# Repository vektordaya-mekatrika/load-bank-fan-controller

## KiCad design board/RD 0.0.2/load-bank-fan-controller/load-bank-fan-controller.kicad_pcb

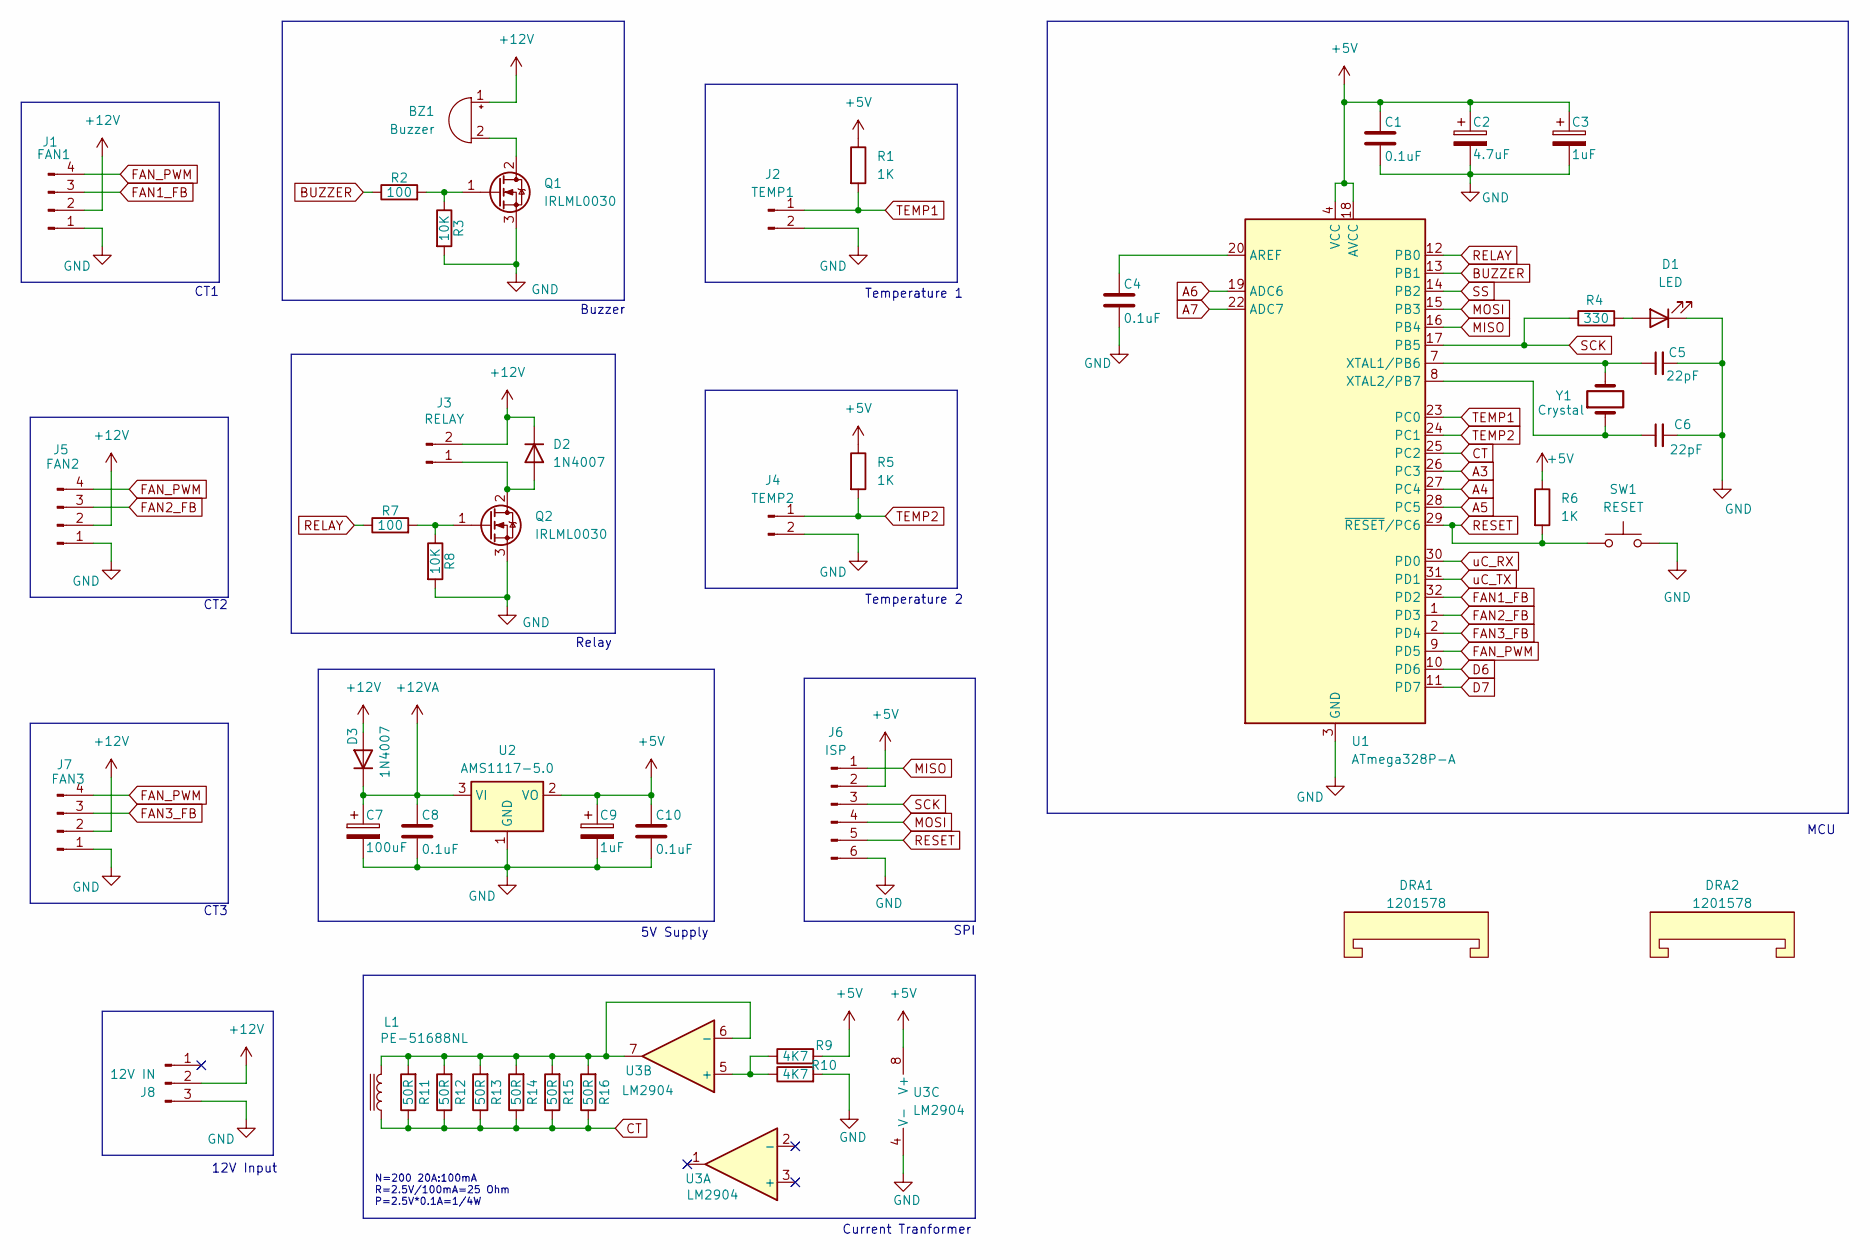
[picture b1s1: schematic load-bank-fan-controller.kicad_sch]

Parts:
BZ1: Buzzer; Buzzer_12x9.5RM7.6; Mfg PN TMB12A12; LCSC Part # DNP
C1, C4, C8, C10: 0.1uF; C_0603_1608Metric_Pad1.08x0.95mm_HandSolder; Mfg PN CC0603KRX7R8BB104; LCSC Part # C92490
C2: 4.7uF; C_0603_1608Metric_Pad1.08x0.95mm_HandSolder; Mfg PN CC0603KRX5R8BB475; LCSC Part # C326580
C3, C9: 1uF; C_0603_1608Metric_Pad1.08x0.95mm_HandSolder; Mfg PN CC0603KRX5R8BB105; LCSC Part # C14664
C5, C6: 22pF; C_0603_1608Metric_Pad1.08x0.95mm_HandSolder; Mfg PN CC0603JRNPO9BN220; LCSC Part # C105620
C7: 100uF; C_1210_3225Metric; Mfg PN EMK325ABJ107MM-T; LCSC Part # C394395
D1: LED; LED_0603_1608Metric_Pad1.05x0.95mm_HandSolder; Mfg PN LTST-C190GKT; LCSC Part # C125093
D2, D3: 1N4007; D_SOD-123F; Mfg PN 1N4007 A7; LCSC Part # C2902912
DRA1, DRA2: 1201578; DINRailAdapter_3xM3_PhoenixContact_1201578; Mfg PN 1201578; LCSC Part # C3019632
J1: FAN1; Molex_KK-254_AE-6410-04A_1x04_P2.54mm_Vertical; Mfg PN XD-2510-4A; LCSC Part # C17700994
J2: TEMP1; JST_XH_B2B-XH-A_1x02_P2.50mm_Vertical; Mfg PN ZX-XH2.54-2PZZ; LCSC Part # DNP
J3: RELAY; TerminalBlock_RND_205-00232_1x02_P5.08mm_Horizontal; Mfg PN WJ500V-5.08-2P; LCSC Part # C8465
J4: TEMP2; JST_XH_B2B-XH-A_1x02_P2.50mm_Vertical; Mfg PN ZX-XH2.54-2PZZ; LCSC Part # DNP
J5: FAN2; Molex_KK-254_AE-6410-04A_1x04_P2.54mm_Vertical; Mfg PN XD-2510-4A; LCSC Part # C17700994
J6: ISP; PinHeader_2x03_P2.54mm_Vertical; Mfg PN ZX-PZ2.54-2-3PZZ; LCSC Part # C7501274
J7: FAN3; Molex_KK-254_AE-6410-04A_1x04_P2.54mm_Vertical; Mfg PN XD-2510-4A; LCSC Part # DNP
J8: 12V IN; JST_VH_B3P-VH-B_1x03_P3.96mm_Vertical; Mfg PN HX VH3.96-3P ZZ; LCSC Part # C7435583
L1: PE-51688NL; PE51688NL; Mfg PN PE-51688NL; LCSC Part # C5718373
Q1, Q2: IRLML0030; SOT-23; Mfg PN IRLML0030TRPBF; LCSC Part # C67272
R1, R5, R6: 1K; R_0603_1608Metric_Pad0.98x0.95mm_HandSolder; Mfg PN RC0603FR-071KL; LCSC Part # C22548
R2, R7: 100; R_0603_1608Metric_Pad0.98x0.95mm_HandSolder; Mfg PN RC0603FR-07100RL; LCSC Part # C105588
R3, R8: 10K; R_0603_1608Metric_Pad0.98x0.95mm_HandSolder; Mfg PN RC0603FR-0710KL; LCSC Part # C98220
R4: 330; R_0603_1608Metric_Pad0.98x0.95mm_HandSolder; Mfg PN RC0603FR-07330RL; LCSC Part # C105881
R9, R10: 4K7; R_0603_1608Metric_Pad0.98x0.95mm_HandSolder; Mfg PN RC0603FR-074K7L; LCSC Part # C99782
R11, R12, R13, R14, R15, R16: 50R; R_MiniMELF_MMA-0204; Mfg PN CSR0204FTDV0500; LCSC Part # C489412
SW1: RESET; SW_Tactile_SPST_NO_Straight_CK_PTS636Sx25SMTRLFS; Mfg PN TS-1101-C-W; LCSC Part # C318938
U1: ATmega328P-A; TQFP-32_7x7mm_P0.8mm; Mfg PN ATmega328P-A; LCSC Part # C14877
U2: AMS1117-5.0; SOT-223-3_TabPin2; Mfg PN AMS1117-5.0; LCSC Part # C6187
U3: LM2904; SO-8_3.9x4.9mm_P1.27mm; Mfg PN LM2904DT; LCSC Part # C105411
Y1: Crystal; Crystal_HC49-U_Vertical; Mfg PN X49SD16MSD2SC; LCSC Part # C16212

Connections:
+5V: C1.1, C2.1, C3.1, C9.1, C10.1, J6.2, R1.1, R5.1, R6.1, R9.2, U1.4 (VCC), U1.6 (VCC), U1.18 (AVCC), U2.2 (VO), U3.8 (V+)
+12V: BZ1.1 (+), D2.1 (K), D3.2 (A), J1.2, J3.2, J5.2, J7.2, J8.2
+12VA: C7.1, C8.1, D3.1 (K), U2.3 (VI)
A3: U1.26 (PC3)
A4: U1.27 (PC4)
A5: U1.28 (PC5)
A6: U1.19 (ADC6)
A7: U1.22 (ADC7)
BUZZER: R2.1, U1.13 (PB1)
CT: L1.1, R11.1, R12.1, R13.1, R14.1, R15.1, R16.1, U1.25 (PC2)
D6: U1.10 (PD6)
D7: U1.11 (PD7)
FAN1_FB: J1.3, U1.32 (PD2)
FAN2_FB: J5.3, U1.1 (PD3)
FAN3_FB: J7.3, U1.2 (PD4)
FAN_PWM: J1.4, J5.4, J7.4, U1.9 (PD5)
GND: C1.2, C2.2, C3.2, C4.2, C5.2, C6.2, C7.2, C8.2, C9.2, C10.2, D1.1 (K), J1.1, J2.2, J4.2, J5.1, J6.6, J7.1, J8.3, Q1.3 (S), Q2.3 (S), R3.2, R8.2, R10.2, SW1.2, U1.3 (GND), U1.5 (GND), U1.21 (GND), U2.1 (GND), U3.4 (V-)
MISO: J6.1, U1.16 (PB4)
MOSI: J6.4, U1.15 (PB3)
unnamed: BZ1.2 (-), Q1.2 (D)
unnamed: D1.2 (A), R4.2
unnamed: D2.2 (A), J3.1, Q2.2 (D)
unnamed: Q1.1 (G), R2.2, R3.1
unnamed: Q2.1 (G), R7.2, R8.1
unnamed: C4.1, U1.20 (AREF)
unnamed: C5.1, U1.7 (XTAL1/PB6), Y1.2
unnamed: C6.1, U1.8 (XTAL2/PB7), Y1.1
unnamed: R9.1, R10.1, U3.5 (+)
unnamed: L1.2, R11.2, R12.2, R13.2, R14.2, R15.2, R16.2, U3.6 (-), U3.7
RELAY: R7.1, U1.12 (PB0)
RESET: J6.5, R6.2, SW1.1, U1.29 (~RESET/PC6)
SCK: J6.3, R4.1, U1.17 (PB5)
SS: U1.14 (PB2)
TEMP1: J2.1, R1.2, U1.23 (PC0)
TEMP2: J4.1, R5.2, U1.24 (PC1)
uC_RX: U1.30 (PD0)
uC_TX: U1.31 (PD1)

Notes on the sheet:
CT2
Current Tranformer
Temperature 1
12V Input
CT3
Buzzer
CT1
Relay
N=200 20A:100mA R=2.5V/100mA=25 Ohm P=2.5V*0.1A=1/4W
Temperature 2
5V Supply
SPI
MCU

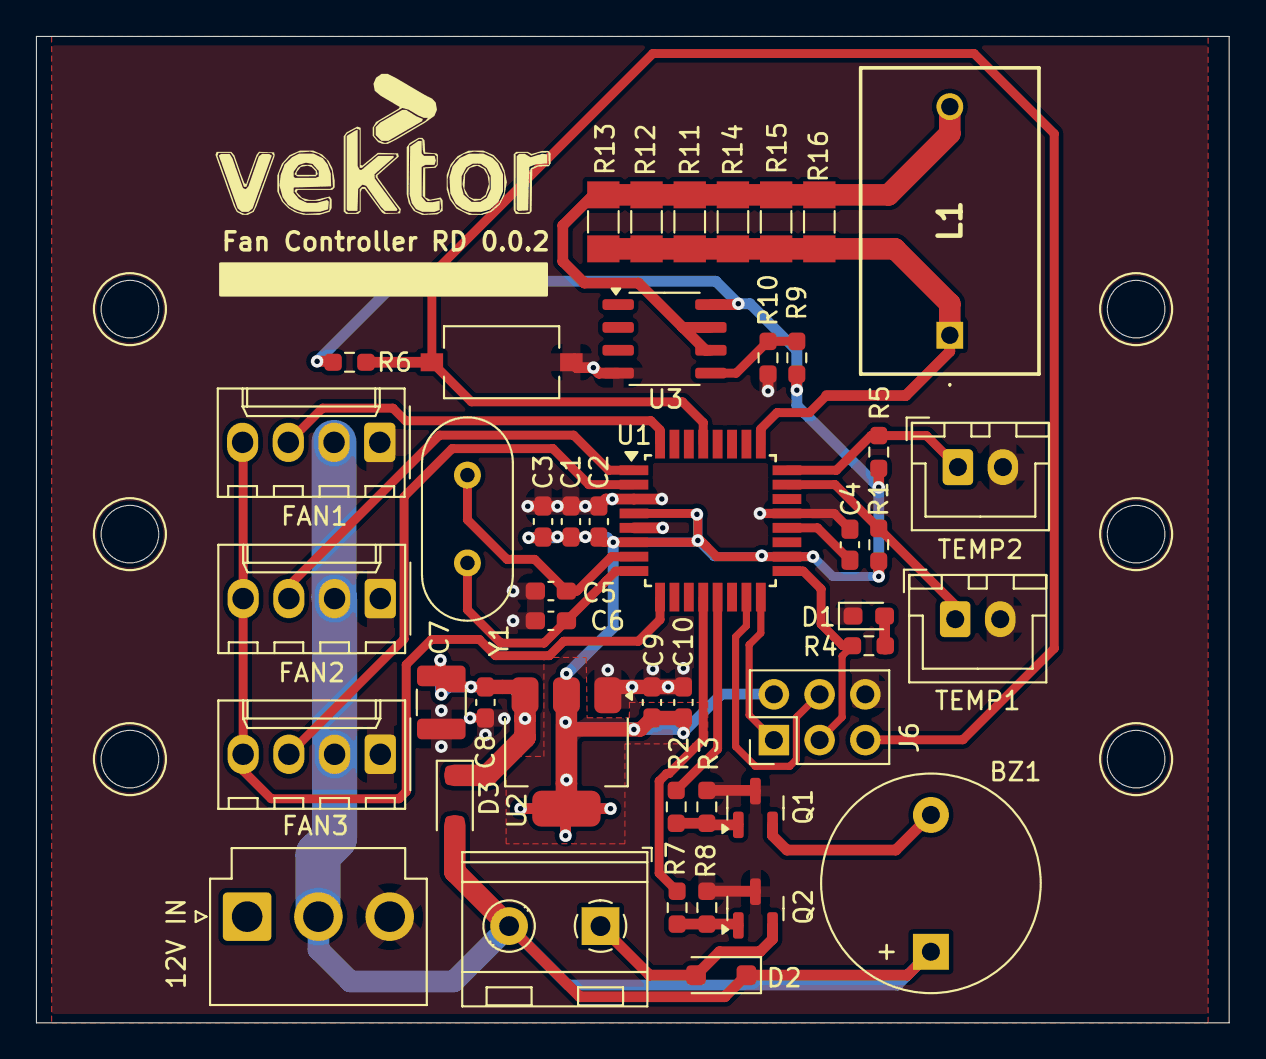
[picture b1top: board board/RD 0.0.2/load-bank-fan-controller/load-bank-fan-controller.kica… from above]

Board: 2 copper layers, 66.3 x 54.8 mm, 48 parts (0 on the bottom side), 27 nets.

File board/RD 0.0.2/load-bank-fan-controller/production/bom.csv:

Designator,Footprint,Quantity,Value,LCSC Part #
BZ1,Buzzer_12x9.5RM7.6,1,Buzzer,DNP
"C1, C10, C4, C8",0603,4,0.1uF,C92490
C2,0603,1,4.7uF,C326580
"C3, C9",0603,2,1uF,C14664
"C5, C6",0603,2,22pF,C105620
C7,1210,1,100uF,C394395
D1,0603,1,LED,C125093
"D2, D3",D_SOD-123F,2,1N4007,C2902912
"DRA1, DRA2",DINRailAdapter_3xM3_PhoenixContact_1201578,2,1201578,C3019632
J1,Molex_KK-254_AE-6410-04A_1x04_P2.54mm_Vertical,1,FAN1,C17700994 
J2,JST_XH_B2B-XH-A_1x02_P2.50mm_Vertical,1,TEMP1,DNP
J3,TerminalBlock_RND_205-00232_1x02_P5.08mm_Horizontal,1,RELAY, C8465
J4,JST_XH_B2B-XH-A_1x02_P2.50mm_Vertical,1,TEMP2,DNP
J5,Molex_KK-254_AE-6410-04A_1x04_P2.54mm_Vertical,1,FAN2,C17700994 
J6,PinHeader_2x03_P2.54mm_Vertical,1,ISP,C7501274
J7,Molex_KK-254_AE-6410-04A_1x04_P2.54mm_Vertical,1,FAN3,DNP
J8,JST_VH_B3P-VH-B_1x03_P3.96mm_Vertical,1,12V IN, C7435583
L1,PE51688NL,1,PE-51688NL,C5718373
"Q1, Q2",SOT-23,2,IRLML0030,C67272
"R1, R5, R6",0603,3,1K,C22548
"R10, R9",0603,2,4K7,C99782
"R11, R12, R13, R14, R15, R16",R_MiniMELF_MMA-0204,6,50R, C489412
"R2, R7",0603,2,100,C105588
"R3, R8",0603,2,10K,C98220
R4,0603,1,330,C105881
SW1,SW_Tactile_SPST_NO_Straight_CK_PTS636Sx25SMTRLFS,1,RESET,C318938
U1,TQFP-32_7x7mm_P0.8mm,1,ATmega328P-A,C14877
U2,SOT-223-3_TabPin2,1,AMS1117-5.0,C6187
U3,SO-8_3.9x4.9mm_P1.27mm,1,LM2904,C105411
Y1,Crystal_HC49-U_Vertical,1,Crystal, C16212

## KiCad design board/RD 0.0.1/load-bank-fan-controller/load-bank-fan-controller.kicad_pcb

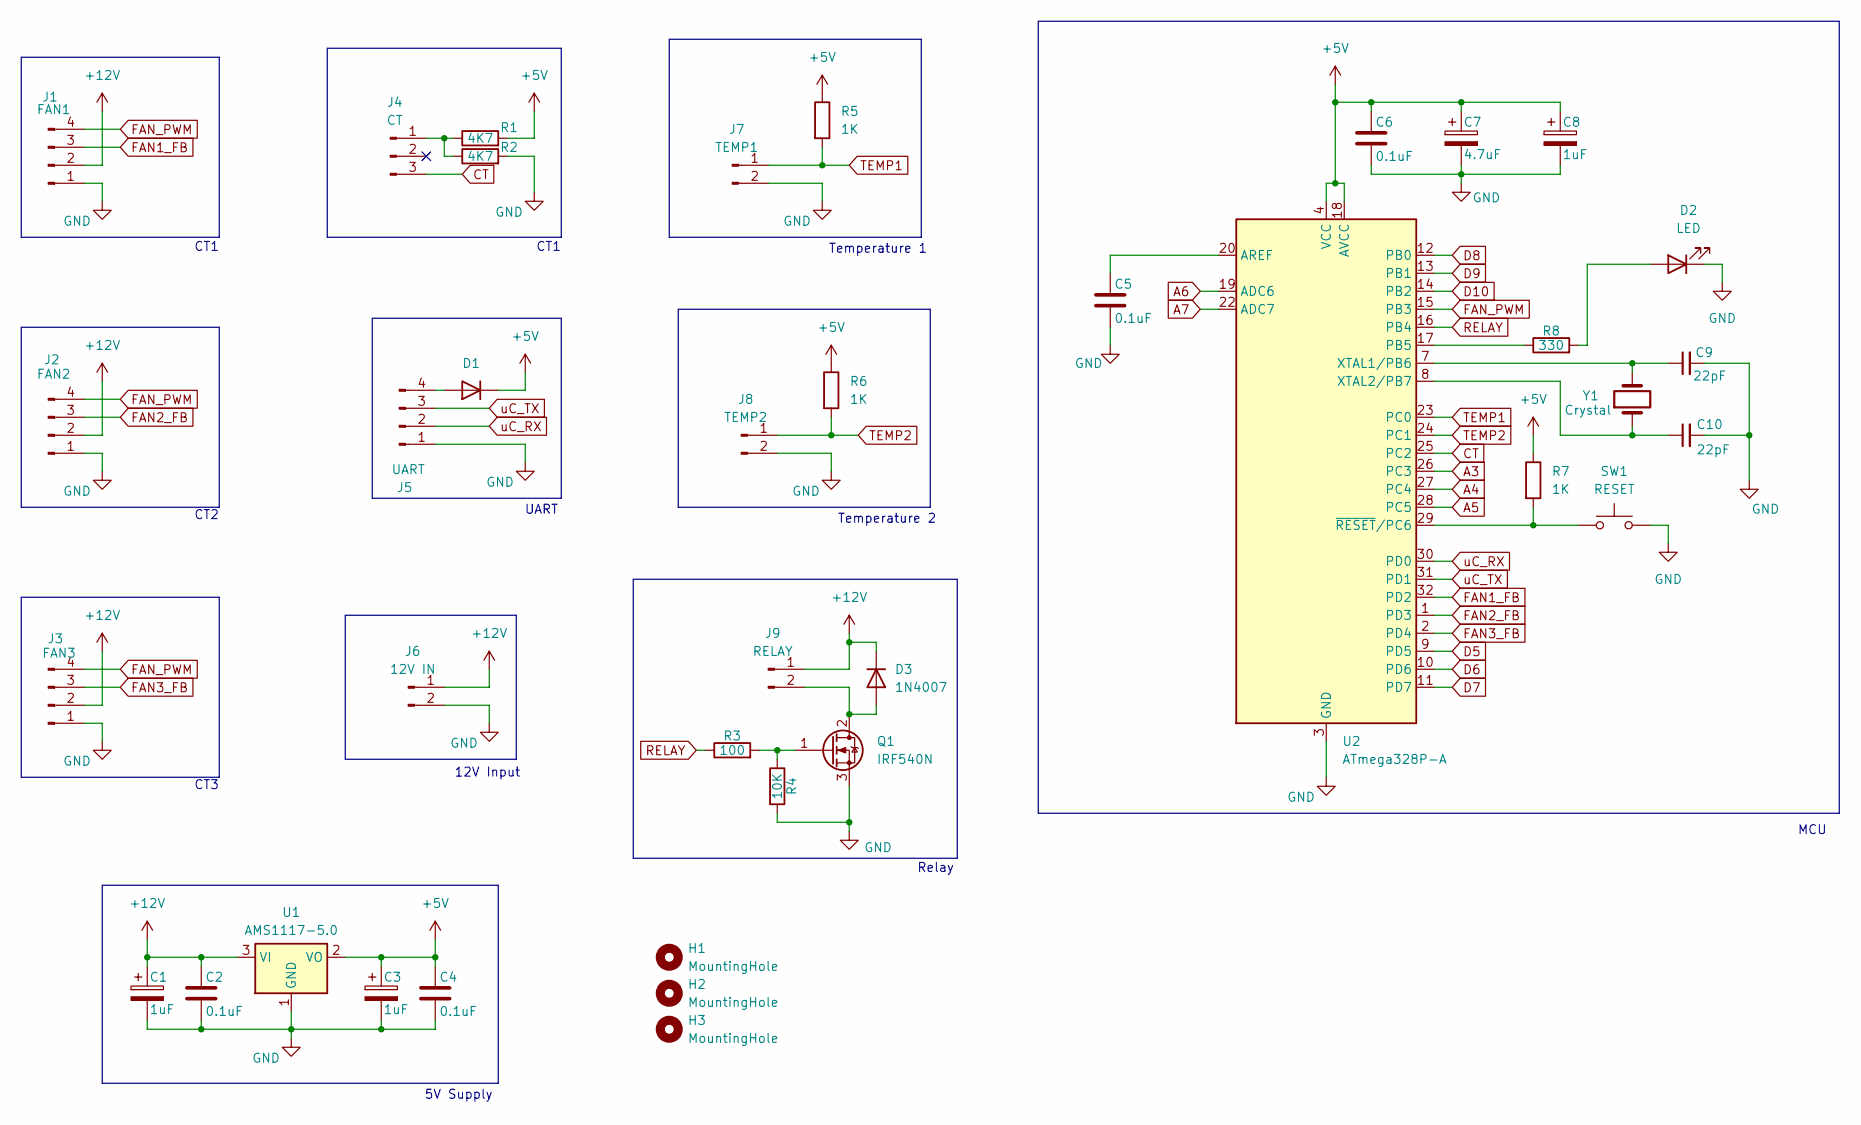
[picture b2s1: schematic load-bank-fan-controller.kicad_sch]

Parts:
C1, C3, C8: 1uF; C_0603_1608Metric_Pad1.08x0.95mm_HandSolder; Mfg PN CC0603KRX5R8BB105; LCSC Part # C14664
C2, C4, C5, C6: 0.1uF; C_0603_1608Metric_Pad1.08x0.95mm_HandSolder; Mfg PN CC0603KRX7R8BB104; LCSC Part # C92490
C7: 4.7uF; C_0603_1608Metric_Pad1.08x0.95mm_HandSolder; Mfg PN CC0603KRX5R8BB475; LCSC Part # C326580
C9, C10: 22pF; C_0603_1608Metric_Pad1.08x0.95mm_HandSolder; Mfg PN CC0603JRNPO9BN220; LCSC Part # C105620
D1: Safety Diode; D_SOD-523; Mfg PN RB521S30T1G; LCSC Part # C145179
D2: LED; LED_0603_1608Metric_Pad1.05x0.95mm_HandSolder; Mfg PN LTST-C190GKT; LCSC Part # C125093
D3: 1N4007; D_SOD-123F; Mfg PN 1N4007 A7; LCSC Part # C2902912
H1, H2, H3: MountingHole; MountingHole_3.2mm_M3
J1: FAN1; Molex_KK-254_AE-6410-04A_1x04_P2.54mm_Vertical; Mfg PN 470531000; LCSC Part # C240840
J2: FAN2; Molex_KK-254_AE-6410-04A_1x04_P2.54mm_Vertical; Mfg PN 470531000; LCSC Part # C240840
J3: FAN3; Molex_KK-254_AE-6410-04A_1x04_P2.54mm_Vertical; Mfg PN 470531000; LCSC Part # C240840
J4: CT; JST_XH_B3B-XH-A_1x03_P2.50mm_Vertical; Mfg PN ZX-XH2.54-3PZZ; LCSC Part # C7429633
J5: UART; JST_XH_B4B-XH-A_1x04_P2.50mm_Vertical; Mfg PN ZX-XH2.54-4PZZ; LCSC Part # C7429634
J6: 12V IN; TerminalBlock_RND_205-00232_1x02_P5.08mm_Horizontal; Mfg PN WJ500V-5.08-2P; LCSC Part # C8465
J7: TEMP1; JST_XH_B2B-XH-A_1x02_P2.50mm_Vertical; Mfg PN ZX-XH2.54-2PZZ; LCSC Part # C7429632
J8: TEMP2; JST_XH_B2B-XH-A_1x02_P2.50mm_Vertical; Mfg PN ZX-XH2.54-2PZZ; LCSC Part # C7429632
J9: RELAY; TerminalBlock_RND_205-00232_1x02_P5.08mm_Horizontal; Mfg PN WJ500V-5.08-2P; LCSC Part # C8465
Q1: IRF540N; TO-220-3_Horizontal_TabDown; Mfg PN IRF540NPBF; LCSC Part # C2566
R1, R2: 4K7; R_0603_1608Metric_Pad0.98x0.95mm_HandSolder; Mfg PN RC0603FR-074K7L; LCSC Part # C99782
R3: 100; R_0603_1608Metric_Pad0.98x0.95mm_HandSolder; Mfg PN RC0603FR-07100RL; LCSC Part # C105588
R4: 10K; R_0603_1608Metric_Pad0.98x0.95mm_HandSolder; Mfg PN RC0603FR-0710KL; LCSC Part # C98220
R5, R6, R7: 1K; R_0603_1608Metric_Pad0.98x0.95mm_HandSolder; Mfg PN RC0603FR-071KL; LCSC Part # C22548
R8: 330; R_0603_1608Metric_Pad0.98x0.95mm_HandSolder; Mfg PN RC0603FR-07330RL; LCSC Part # C105881
SW1: RESET; SW_Tactile_SPST_NO_Straight_CK_PTS636Sx25SMTRLFS; Mfg PN TS-1101-C-W; LCSC Part # C318938
U1: AMS1117-5.0; SOT-223-3_TabPin2; Mfg PN AMS1117-5.0; LCSC Part # C6187
U2: ATmega328P-A; TQFP-32_7x7mm_P0.8mm; Mfg PN ATmega328P-A; LCSC Part # C14877
Y1: Crystal; Crystal_HC49-U_Vertical; Mfg PN X49SD16MSD2SC; LCSC Part # C16212

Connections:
+5V: C3.1, C4.1, C6.1, C7.1, C8.1, D1.1 (K), R1.2, R5.1, R6.1, R7.1, U1.2 (VO), U2.4 (VCC), U2.6 (VCC), U2.18 (AVCC)
+12V: C1.1, C2.1, D3.1 (K), J1.2, J2.2, J3.2, J6.1, J9.1, U1.3 (VI)
A3: U2.26 (PC3)
A4: U2.27 (PC4)
A5: U2.28 (PC5)
A6: U2.19 (ADC6)
A7: U2.22 (ADC7)
CT: J4.3, U2.25 (PC2)
D5: U2.9 (PD5)
D6: U2.10 (PD6)
D7: U2.11 (PD7)
D8: U2.12 (PB0)
D9: U2.13 (PB1)
D10: U2.14 (PB2)
FAN1_FB: J1.3, U2.32 (PD2)
FAN2_FB: J2.3, U2.1 (PD3)
FAN3_FB: J3.3, U2.2 (PD4)
FAN_PWM: J1.4, J2.4, J3.4, U2.15 (PB3)
GND: C1.2, C2.2, C3.2, C4.2, C5.2, C6.2, C7.2, C8.2, C9.2, C10.2, D2.1 (K), J1.1, J2.1, J3.1, J5.1, J6.2, J7.2, J8.2, Q1.3 (S), R2.2, R4.2, SW1.2, U1.1 (GND), U2.3 (GND), U2.5 (GND), U2.21 (GND)
unnamed: D1.2 (A), J5.4
unnamed: D2.2 (A), R8.2
unnamed: D3.2 (A), J9.2, Q1.2 (D)
unnamed: J4.1, R1.1, R2.1
unnamed: Q1.1 (G), R3.2, R4.1
unnamed: C5.1, U2.20 (AREF)
unnamed: R8.1, U2.17 (PB5)
unnamed: C9.1, U2.7 (XTAL1/PB6), Y1.2
unnamed: C10.1, U2.8 (XTAL2/PB7), Y1.1
unnamed: R7.2, SW1.1, U2.29 (~RESET/PC6)
RELAY: R3.1, U2.16 (PB4)
TEMP1: J7.1, R5.2, U2.23 (PC0)
TEMP2: J8.1, R6.2, U2.24 (PC1)
uC_RX: J5.2, U2.30 (PD0)
uC_TX: J5.3, U2.31 (PD1)

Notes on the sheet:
CT2
CT1
Temperature 1
12V Input
CT3
UART
Relay
Temperature 2
5V Supply
MCU

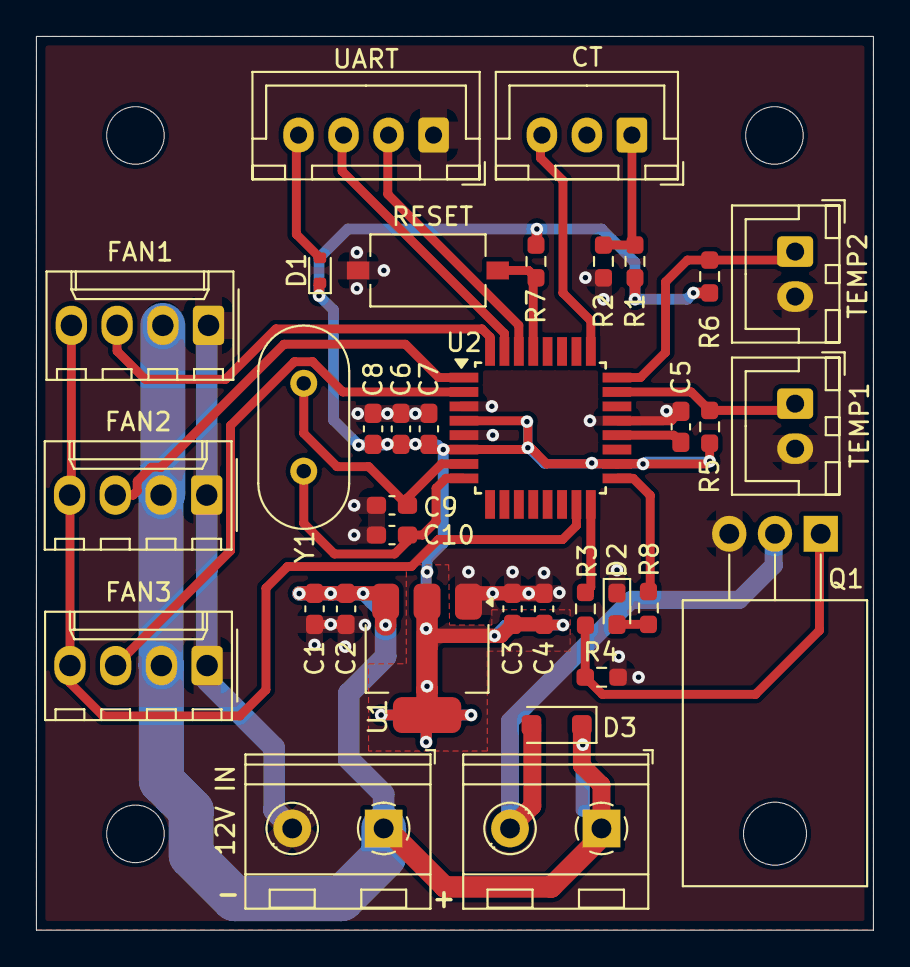
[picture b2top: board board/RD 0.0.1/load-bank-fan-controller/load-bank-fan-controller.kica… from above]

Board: 2 copper layers, 46.5 x 49.7 mm, 38 parts (0 on the bottom side), 23 nets.

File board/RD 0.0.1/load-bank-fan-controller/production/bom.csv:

Designator,Footprint,Quantity,Value,LCSC Part #
"C1, C3, C8",0603,3,1uF,C14664
"C10, C9",0603,2,22pF,C105620
"C2, C4, C5, C6",0603,4,0.1uF,C92490
C7,0603,1,4.7uF,C326580
D1,D_SOD-523,1,Safety Diode,C145179
D2,0603,1,LED,C125093
D3,D_SOD-123F,1,1N4007,C2902912
J1,Molex_KK-254_AE-6410-04A_1x04_P2.54mm_Vertical,1,FAN1,C240840
J2,Molex_KK-254_AE-6410-04A_1x04_P2.54mm_Vertical,1,FAN2,C240840
J3,Molex_KK-254_AE-6410-04A_1x04_P2.54mm_Vertical,1,FAN3,C240840
J4,JST_XH_B3B-XH-A_1x03_P2.50mm_Vertical,1,CT,C7429633
J5,JST_XH_B4B-XH-A_1x04_P2.50mm_Vertical,1,UART,C7429634
J6,TerminalBlock_RND_205-00232_1x02_P5.08mm_Horizontal,1,12V IN, C8465
J7,JST_XH_B2B-XH-A_1x02_P2.50mm_Vertical,1,TEMP1,C7429632
J8,JST_XH_B2B-XH-A_1x02_P2.50mm_Vertical,1,TEMP2,C7429632
J9,TerminalBlock_RND_205-00232_1x02_P5.08mm_Horizontal,1,RELAY, C8465
Q1,TO-220-3_Horizontal_TabDown,1,IRF540N,C2566
"R1, R2",0603,2,4K7,C99782
R3,0603,1,100,C105588
R4,0603,1,10K,C98220
"R5, R6, R7",0603,3,1K,C22548
R8,0603,1,330,C105881
SW1,SW_Tactile_SPST_NO_Straight_CK_PTS636Sx25SMTRLFS,1,RESET,C318938
U1,SOT-223-3_TabPin2,1,AMS1117-5.0,C6187
U2,TQFP-32_7x7mm_P0.8mm,1,ATmega328P-A,C14877
Y1,Crystal_HC49-U_Vertical,1,Crystal, C16212

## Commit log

2024-09-13 finish board routing
2024-09-25 change pin assignment
2024-09-25 add code to reset rpm
2024-09-25 add code for relay and tidy up the code
2024-09-25 move the files to deeper folder
2024-09-26 first commit for the RD 0.0.2
    add buzzer, spi conn, onboard CT, din rail mount adapter, change some conn and FET
2024-09-26 minor editting
2024-09-27 replace current sense resistor with the proper one
2024-09-27 connector changed and component added
    change 12v connector, change spi to icsp connector, change regulator input cap to 100u, remove uart conn, add diode to regulator input
2024-10-01 straighten the din rail mount
2024-10-14 update the production file, and reverse the relay ops in the code
2024-10-17 change wrong footprint from L_1210 to C_1210
2024-11-08 edit pin assignment
